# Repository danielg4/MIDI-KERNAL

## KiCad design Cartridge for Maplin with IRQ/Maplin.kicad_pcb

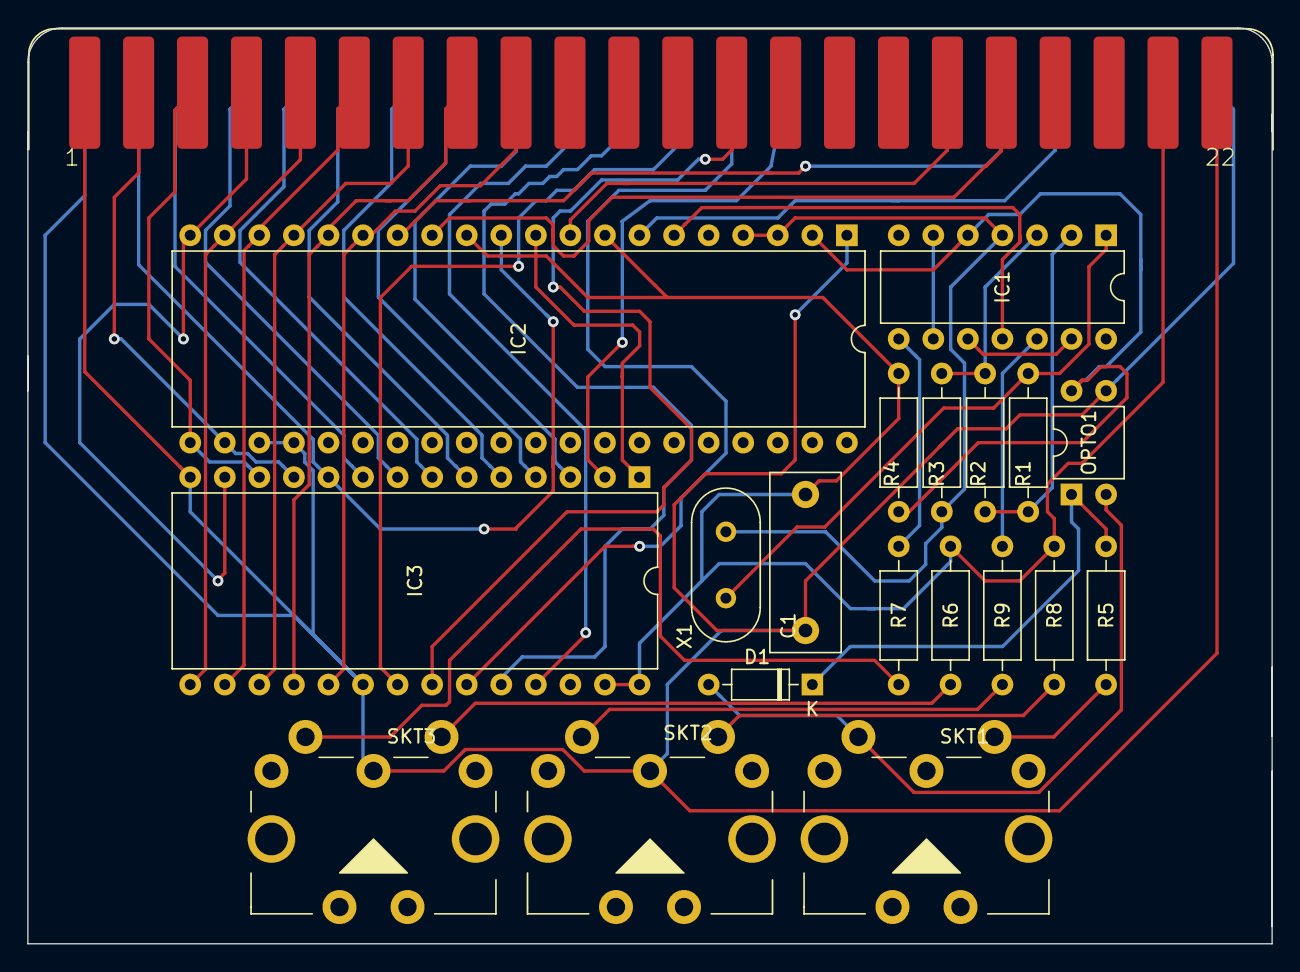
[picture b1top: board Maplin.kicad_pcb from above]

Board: 2 copper layers, 91.4 x 67.3 mm, 20 parts (0 on the bottom side), 45 nets.

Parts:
C1: 100nF; C_Rect_L13.0mm_W5.0mm_P10.00mm_FKS3_FKP3_MKS4
D1: 1N4148; D_DO-35_SOD27_P7.62mm_Horizontal
IC1: 74LS04; DIP-14_W7.62mm
IC2: MC6850; DIP-40_W15.24mm
IC3: 2764; DIP-28_W15.24mm
OPTO1: SFH617A-3; DIP-4_W7.62mm
P1: EXPANSIONPORT-VIC20-EDGE; MA156-22-2
R1, R3: 2k2; R_Axial_DIN0207_L6.3mm_D2.5mm_P10.16mm_Horizontal
R2, R5, R6, R7, R8, R9: 220R; R_Axial_DIN0207_L6.3mm_D2.5mm_P10.16mm_Horizontal
R4: 4k7; R_Axial_DIN0207_L6.3mm_D2.5mm_P10.16mm_Horizontal
SKT1: MIDI_IN; DIN5_MIDI
SKT2: MIDI_OUT; DIN5_MIDI
SKT3: MIDI_THRU; DIN5_MIDI
X1: 2MHz; Crystal_HC49-U_Vertical

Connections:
+5V: C1.1, IC2.8, IC2.10, IC2.12, IC3.1, IC3.27, IC3.28, P1.21, R4.1, R6.1, R8.1
/A1: IC3.9, P1.C
/A2: IC3.8, P1.D
/A3: IC3.7, P1.E
/A4: IC3.6, P1.F
/A5: IC3.5, P1.H
/A6: IC3.4, P1.J
/A7: IC3.3, P1.K
/A8: IC3.25, P1.L
/A9: IC3.24, P1.M
/A10: IC3.21, P1.N
/A11: IC3.23, P1.P
/A12: IC3.2, P1.R
/D0: IC2.22, IC3.11, P1.2
/D1: IC2.21, IC3.12, P1.3
/D2: IC2.20, IC3.13, P1.4
/D3: IC2.19, IC3.15, P1.5
/D4: IC2.18, IC3.16, P1.6
/D5: IC2.17, IC3.17, P1.7
/D6: IC2.16, IC3.18, P1.8
/D7: IC2.15, IC3.19, P1.9
BLK5: IC3.22, P1.13
CA0: IC2.11, IC3.10, P1.B
GND: C1.2, IC2.1, IC2.23, IC2.24, IC3.14, IC3.20, OPTO1.3, P1.1, P1.22, P1.A, P1.Z, SKT2.2, SKT3.2
IO3: IC2.9, P1.17
unnamed: D1.1, OPTO1.1, R5.1
unnamed: D1.2, OPTO1.2, SKT1.5
unnamed: IC1.1, R1.1, X1.1
unnamed: IC1.2, R1.2, R2.1
unnamed: IC1.3, R2.2, R3.1
unnamed: IC1.4, IC2.3, IC2.4, R3.2, X1.2
unnamed: IC1.5, IC2.2, OPTO1.4, R4.2
unnamed: IC1.6, IC1.9
unnamed: IC1.8, R7.1
unnamed: IC1.10, IC1.13
unnamed: IC1.11, IC2.6
unnamed: IC1.12, R9.1
unnamed: IC2.7, P1.W
unnamed: R5.2, SKT1.4
unnamed: R6.2, SKT3.4
unnamed: R7.2, SKT3.5
unnamed: R8.2, SKT2.4
unnamed: R9.2, SKT2.5
R_W: IC2.13, P1.18
S02: IC2.14, P1.V

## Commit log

2026-01-28 https://sleepingelephant.com/ipw-web/bulletin/bb/viewtopic.php?p=125248#p125248
2026-02-08 Make synth demo use three voices instead of one
2026-02-08 Add hypothetical Maplin interface with IRQ to KERNAL & PAL timings to synth demo PAL version sounds just wrong, though
2026-02-09 Fix PAL timing in synth demo, Maplin goofs, and VIC-MIDI non-support
2026-02-10 Make it actually build without errors
2026-03-22 Implement note priority and fix more goofs
2026-03-23 Add fourth voice and de-goof again
